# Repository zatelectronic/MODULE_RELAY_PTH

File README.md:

<div align="center">

# MODULE RELAY

**Módulo de relé com acionamento por nível alto (High Level Trigger), componentes totalmente através-furo (PTH), optoacoplador PC817 e relé de potência 12VDC / 15A**

</div>

---

## 📋 Índice

- [MODULE RELAY](#module-relay)
  - [📋 Índice](#-índice)
  - [Visão Geral](#visão-geral)
  - [Imagens do Projeto](#imagens-do-projeto)
  - [Diferenças em relação ao MODULE RELAY SMD](#diferenças-em-relação-ao-module-relay-smd)
  - [Funcionalidades](#funcionalidades)
  - [Diagrama de Funcionamento](#diagrama-de-funcionamento)
  - [Especificações Técnicas](#especificações-técnicas)
  - [Lista de Materiais](#lista-de-materiais)
  - [Pinagem dos Conectores](#pinagem-dos-conectores)
    - [J1 — Entrada (Controle)](#j1--entrada-controle)
    - [J2 — Saída (Carga)](#j2--saída-carga)
  - [Aplicações](#aplicações)
  - [Estrutura do Repositório](#estrutura-do-repositório)
  - [Como Usar](#como-usar)
    - [Conexão básica com Arduino / ESP32](#conexão-básica-com-arduino--esp32)
    - [Exemplo de código Arduino](#exemplo-de-código-arduino)
    - [Dica de Montagem](#dica-de-montagem)
  - [⚠️ Avisos de Segurança](#️-avisos-de-segurança)
  - [Sobre](#sobre)

---

## Visão Geral

**MODULE RELAY** é um módulo de acionamento de relé com **acionamento por optoacoplador** (a entrada +IN e a bobina usam o mesmo GND do borne J1: não há isolação galvânica entre controle e alimentação; os contatos do relé são isolados da bobina), projetado pela **ZAT ELECTRONIC** utilizando **KiCad 10**. Diferente da versão SMD, esta placa utiliza exclusivamente **componentes através-furo (PTH)**, tornando-a ideal para montagem manual, prototipagem e laboratórios maker.

O circuito utiliza o optoacoplador **PC817** (DIP-4 PTH) para acoplar o sinal de controle (proveniente de microcontroladores como Arduino, ESP32, etc.) do circuito de potência. O transistor **BC548** (TO-92 PTH) aciona a bobina do relé de potência 12VDC, capaz de comutar cargas de até **15A em 125VAC ou 24VDC**.

> ⚡ **High Level Trigger** — o relé é acionado com sinal lógico alto (+3,3V ou +5V) no pino de entrada, com o LED do optoacoplador como carga do pino do microcontrolador.

---

## Imagens do Projeto

<div align="center">

*Vista superior — relé de potência, optoacoplador PC817 DIP, transistor BC548 e bornes KRE*

<br/>

*Vista isométrica — componentes PTH, LED azul 5mm e layout geral da placa*

<br/>

<br/>

<br/>

</div>

---

## Diferenças em relação ao MODULE RELAY SMD

| Característica | MODULE RELAY (PTH) | MODULE RELAY SMD |
|----------------|-------------------|-----------------|
| **Tipo de montagem** | Através-furo (PTH) | Montagem superficial (SMD) |
| **Optoacoplador** | PC817 DIP-4 PTH | LTV-357T SOP-4 SMD |
| **Transistor driver** | BC548 (TO-92 PTH) | MMBT2222A (SOT-23 SMD) |
| **Resistores** | Axial 0,5W PTH | SMD 0805 |
| **LED de status** | 5mm PTH azul | SMD 0805 |
| **Diodo de roda livre** | 1N4007 PTH axial | S1M SMA SMD |
| **Facilidade de montagem** | Alta — soldagem manual simples | Requer soldagem SMD |
| **Público alvo** | Iniciantes, makers, laboratório | Produção, compacto, profissional |

---

## Funcionalidades

- ✅ **Relé de potência 12VDC / 15A** — contatos SPDT (NO, COMUM, NC), 15A 125VAC / 15A 24VDC
- ✅ **Optoacoplador PC817** (DIP-4 PTH) — aciona o driver; controle e bobina compartilham o GND
- ✅ **Transistor BC548** (TO-92 PTH) — driver NPN para acionamento da bobina
- ✅ **Diodo de roda livre 1N4007** (PTH axial) — proteção contra tensão reversa da bobina
- ✅ **LED azul 5mm PTH** — indicação visual de relé acionado
- ✅ **High Level Trigger** — compatível com 3,3V e 5V (Arduino, ESP32, Raspberry Pi, etc.)
- ✅ **Bornes KRE parafuso** (3 pinos, passo 5,0mm) — conexão robusta para entrada e saída
- ✅ **Todos os componentes PTH** — montagem manual fácil, ideal para prototipagem
- ✅ **Made in Brazil** — serigrafia na PCB

---

## Diagrama de Funcionamento

```
Microcontrolador / Sinal de Controle
        │
    +IN ●──[R1 220Ω]──► U1 PC817 (LED, pino 1) ── pino 2 ── GND
                               │ (acoplamento óptico)
    +12V ─────────────► U1 coletor (pino 4)
                        U1 emissor (pino 3) ──[R2 4,7kΩ]──┬──► Base Q1 BC548
                                                        [R4 10kΩ]
                                                          │
                                                         GND
    +12V ──┬──────────────┬─────────[R3 470Ω]──[D1 LED azul]──┐
       [Bobina K1]   [D2 1N4007] (roda livre)                 │
           └──────────────┴───────────────────────────────────┴──► Coletor Q1 (emissor no GND)

              Contatos do Relé (J2 — OUT)
         ┌────────────────────────────────┐
         │   NO  │  COMUM  │  NC          │
         └────────────────────────────────┘
          Carga: até 15A / 125VAC ou 24VDC
```

---

## Especificações Técnicas

| Parâmetro | Valor |
|-----------|-------|
| **Relé** | 12VDC / SPDT (Form C) |
| **Tensão da Bobina** | 12VDC |
| **Corrente máx. de carga (AC)** | 15A @ 125VAC |
| **Corrente máx. de carga (DC)** | 15A @ 24VDC |
| **Tipo de contato** | SPDT — NO, NC, COMUM |
| **Tensão de alimentação do módulo** | +12V |
| **Tensão de controle (sinal IN)** | 3,3V a 5V (High Level Trigger) |
| **Optoacoplador** | PC817 DIP-4 — GND comum com a bobina |
| **Transistor driver** | BC548 (TO-92, NPN) |
| **Diodo de proteção** | 1N4007 (PTH axial) |
| **LED de status** | 5mm PTH azul |
| **Resistores** | Axial 0,5W PTH |
| **Conectores** | Borne KRE parafuso 3 pinos, passo 5,0mm |
| **Ferramenta de Projeto** | KiCad 10 |
| **Tipo de montagem** | PTH — Através-furo |

---

## Lista de Materiais

| Ref | Componente | Valor / Parte | Encapsulamento |
|-----|-----------|--------------|----------------|
| K1 | Relé de Potência | AY1RC2 12VDC / 15A SPDT | PTH (pinagem SANYOU SRD) |
| U1 | Optoacoplador | PC817 | DIP-4 PTH |
| Q1 | Transistor NPN | BC548 | TO-92 PTH |
| D2 | Diodo de Roda Livre | 1N4007 | PTH Axial |
| D1 | LED de Status | LED 5mm Azul | PTH 5mm |
| R1 | Resistor de entrada (LED do opto) | 220Ω | Axial PTH |
| R2 | Resistor série da base | 4,7kΩ | Axial PTH |
| R4 | Resistor pull-down da base | 10kΩ | Axial PTH |
| R3 | Resistor do LED de status | 470Ω | Axial PTH |
| J1 | Borne de Entrada (Controle) | +12V, +IN, GND | KRE 3 pinos 5,0mm |
| J2 | Borne de Saída (Carga) | NO, COMUM, NC | KRE 3 pinos 5,0mm |

---

## Pinagem dos Conectores

### J1 — Entrada (Controle)

| Pino | Sinal | Descrição |
|------|-------|-----------|
| 1 | +12V | Alimentação da bobina do relé |
| 2 | +IN | Sinal de controle (3,3V–5V = relé ON) |
| 3 | GND | Terra comum |

### J2 — Saída (Carga)

| Pino | Sinal | Descrição |
|------|-------|-----------|
| 1 | NO | Normalmente aberto (fecha quando acionado) |
| 2 | COMUM | Terminal comum do relé |
| 3 | NC | Normalmente fechado (abre quando acionado) |

---

## Aplicações

- 🏠 **Automação residencial** — acionamento de lâmpadas, tomadas e ventiladores
- 🤖 **Projetos com Arduino e ESP32** — controle de cargas AC
- 🏫 **Ensino e prototipagem** — componentes PTH facilmente soldáveis e substituíveis
- 💡 **Controle de iluminação** — painéis de LED de alta potência e luminárias
- 🔌 **Comutação de cargas** — relé separa os contatos de carga da bobina (GND de controle e de alimentação é comum)
- 📡 **IoT e domótica** — integração com sistemas MQTT, Home Assistant, etc.

---

## Estrutura do Repositório

```
MODULE_RELAY_PTH/
├── MODULE_RELAY_PTH.kicad_pro    # Arquivo de projeto KiCad 10
├── MODULE_RELAY_PTH.kicad_sch    # Esquemático: capa A2 (índice das folhas)
├── RELAY.kicad_sch               # Folha 02: optoacoplador + driver + relé
├── CONN.kicad_sch                # Folha 03: bornes IN / OUT + PWR_FLAG
├── MODULE_RELAY_PTH.kicad_pcb    # Layout da PCB (KiCad 10)
├── MODULE_RELAY_PTH.kicad_prl    # Configurações locais
├── MODULE_RELAY_PTH.kicad_dru    # Regra: GND a 3 mm dos contatos do relé
├── Zat_TitleBlock.kicad_wks      # Title block ZAT ELECTRONIC
├── packages3D/                   # Modelos 3D arquivados (referência)
├── imagem_1.png                  # Render 3D superior
├── imagem_2.png                  # Render 3D isométrico
├── LEIA-ME_REVISAO_R01.md        # O que mudou na revisão R01
└── README.md
```

---

## Como Usar

### Conexão básica com Arduino / ESP32

```
Arduino / ESP32             MODULE RELAY
───────────────────         ─────────────────
GND              ────────►  J1 - GND
Pino digital     ────────►  J1 - +IN

Fonte 12VDC (+)  ────────►  J1 - +12V
Fonte 12VDC (-)  ────────►  J1 - GND

Carga AC/DC      ────────►  J2 - COMUM + NO (ou NC)
```

### Exemplo de código Arduino

```cpp
#define RELAY_PIN 7

void setup() {
  pinMode(RELAY_PIN, OUTPUT);
  digitalWrite(RELAY_PIN, LOW); // relé desligado na inicialização
}

void loop() {
  digitalWrite(RELAY_PIN, HIGH); // aciona o relé
  delay(1000);
  digitalWrite(RELAY_PIN, LOW);  // desaciona o relé
  delay(1000);
}
```

### Dica de Montagem

> 🔧 Por ser totalmente PTH, recomenda-se a seguinte ordem de soldagem: resistores primeiro, depois diodo, transistor BC548, optoacoplador PC817, LED, relé e por último os bornes KRE.

## ⚠️ Avisos de Segurança

> 🔴 **ATENÇÃO — TENSÕES PERIGOSAS**

- Este módulo pode comutar tensões de **rede elétrica (110V / 220V AC)**. Manuseie com extremo cuidado.
- **Nunca toque nos terminais J2 (OUT)** enquanto houver carga CA conectada e o circuito energizado.
- Utilize **caixa de proteção** adequada quando instalar em ambientes com acesso de pessoas.
- Respeite a **corrente máxima de 15A** nos contatos do relé.
- O optoacoplador **não isola** o GND do microcontrolador do GND do módulo (são comuns no J1) e **não substitui normas de segurança elétrica**.
- A zona GND fica a 3 mm das trilhas e pads dos contatos do relé (COMUM / NO / NC), por regra no MODULE_RELAY_PTH.kicad_dru. Conferir a creepage exigida pela norma da aplicação final.
- Projeto destinado a **profissionais e experimentadores experientes**.

---

## Sobre

<div align="center">

Projetado por **ZAT ELECTRONIC**

*MODULE RELAY — Made in Brazil 🇧🇷*

</div>>

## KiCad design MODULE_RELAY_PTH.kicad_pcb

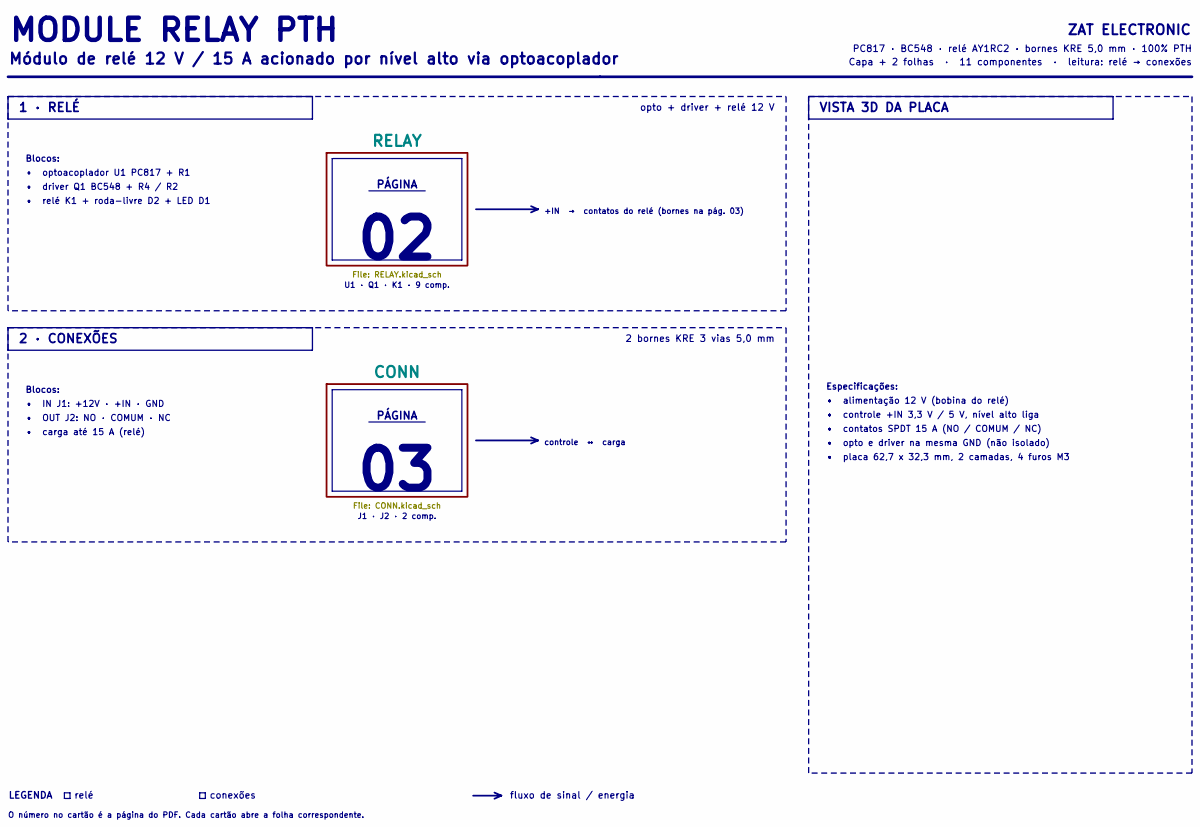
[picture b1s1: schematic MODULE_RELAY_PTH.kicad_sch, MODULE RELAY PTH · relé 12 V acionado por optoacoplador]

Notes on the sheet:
O número no cartão é a página do PDF. Cada cartão abre a folha correspondente.
fluxo de sinal / energia
conexões
controle ↔ carga
• driver Q1 BC548 + R4 / R2
2 bornes KRE 3 vias 5,0 mm
+IN → contatos do relé (bornes na pág. 03)
Blocos:
1 · RELÉ
ZAT ELECTRONIC
Módulo de relé 12 V / 15 A acionado por nível alto via optoacoplador
LEGENDA
J1 · J2 · 2 comp.
• controle +IN 3,3 V / 5 V, nível alto liga
opto + driver + relé 12 V
• opto e driver na mesma GND (não isolado)
• contatos SPDT 15 A (NO / COMUM / NC)
• carga até 15 A (relé)
• OUT J2: NO · COMUM · NC
• relé K1 + roda-livre D2 + LED D1
• optoacoplador U1 PC817 + R1
PC817 · BC548 · relé AY1RC2 · bornes KRE 5,0 mm · 100% PTH
relé
PÁGINA
2 · CONEXÕES
Capa + 2 folhas · 11 componentes · leitura: relé → conexões
• placa 62,7 x 32,3 mm, 2 camadas, 4 furos M3
• alimentação 12 V (bobina do relé)
U1 · Q1 · K1 · 9 comp.
• IN J1: +12V · +IN · GND
MODULE RELAY PTH
Especificações:
VISTA 3D DA PLACA

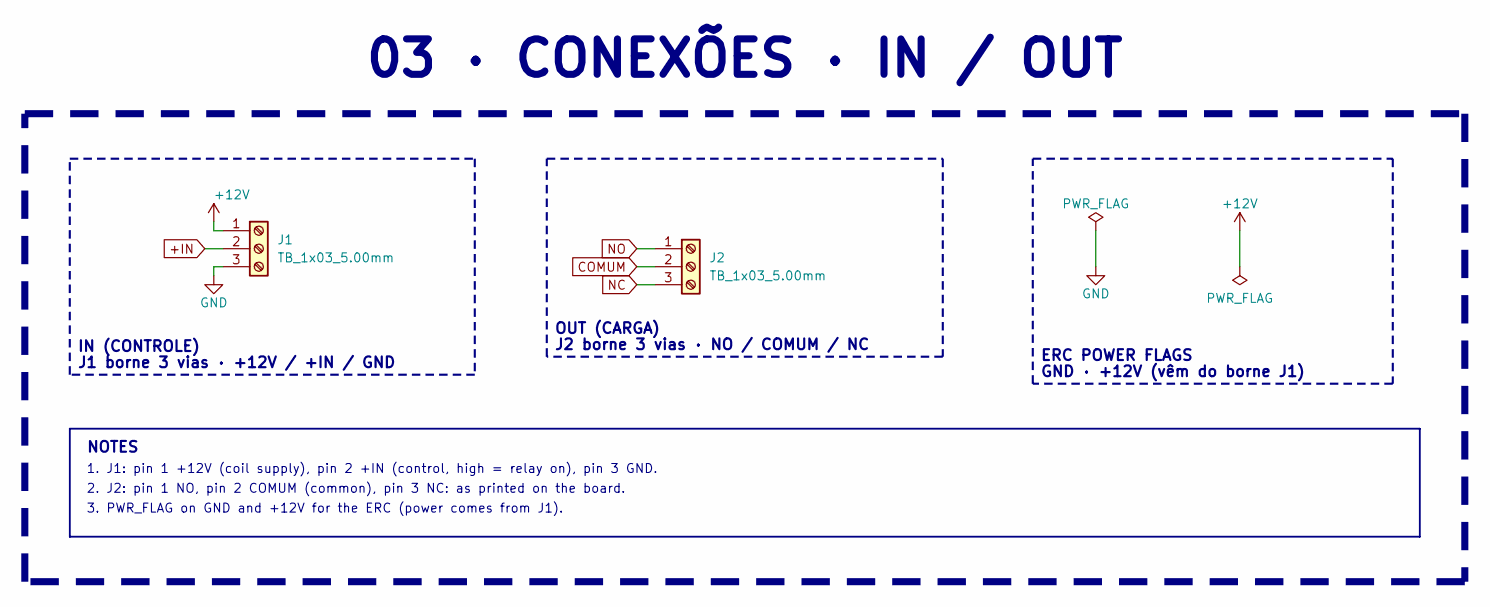
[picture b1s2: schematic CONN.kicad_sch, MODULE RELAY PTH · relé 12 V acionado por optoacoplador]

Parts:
J1, J2: TB_1x03_5.00mm; TerminalBlock_MaiXu_MX126-5.0-03P_1x03_P5.00mm_DG306

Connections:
+12V: J1.1; also elsewhere on the board
+IN: J1.2; also elsewhere on the board
COMUM: J2.2; also elsewhere on the board
GND: J1.3; also elsewhere on the board
NC: J2.3; also elsewhere on the board
NO: J2.1; also elsewhere on the board

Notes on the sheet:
NOTES
1. J1: pin 1 +12V (coil supply), pin 2 +IN (control, high = relay on), pin 3 GND.
3. PWR_FLAG on GND and +12V for the ERC (power comes from J1).
03 · CONEXÕES · IN / OUT
J2 borne 3 vias · NO / COMUM / NC
IN (CONTROLE)
GND · +12V (vêm do borne J1)
OUT (CARGA)
ERC POWER FLAGS
2. J2: pin 1 NO, pin 2 COMUM (common), pin 3 NC: as printed on the board.
J1 borne 3 vias · +12V / +IN / GND

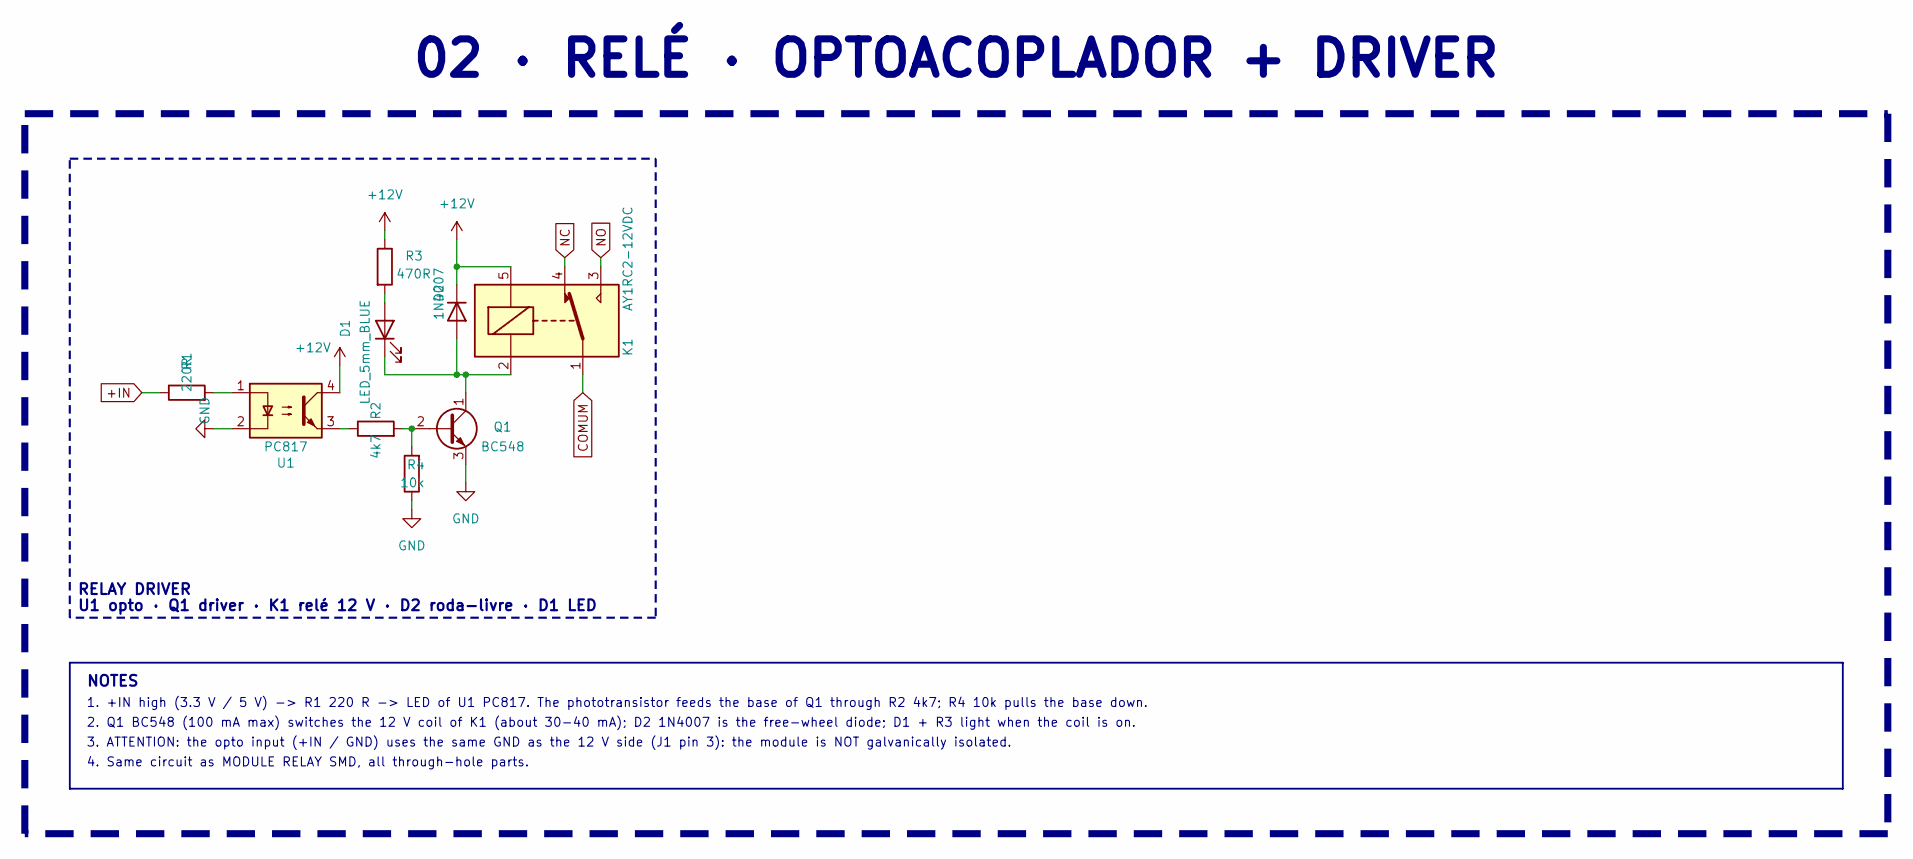
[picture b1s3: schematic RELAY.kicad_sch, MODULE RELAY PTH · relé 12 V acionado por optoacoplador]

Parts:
D1: LED_5mm_BLUE; LED_D5.0mm_Blue
D2: 1N4007; D_DO-41_SOD81_P10.16mm_Horizontal_1N4007
K1: AY1RC2-12VDC; Relay_SPDT_SANYOU_SRD_Series_Form_C_AY1RC2
Q1: BC548; TO-92_HandSolder_BC548
R1: 220R; R_Axial_DIN0204_L3.6mm_D1.6mm_P7.62mm_Horizontal_220R
R2: 4k7; R_Axial_DIN0204_L3.6mm_D1.6mm_P7.62mm_Horizontal_4K7
R3: 470R; R_Axial_DIN0204_L3.6mm_D1.6mm_P7.62mm_Horizontal_470R
R4: 10k; R_Axial_DIN0204_L3.6mm_D1.6mm_P7.62mm_Horizontal_10K
U1: PC817; DIP-4_W7.62mm_LongPads_PC817

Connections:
+12V: D2.1 (K), K1.5, R3.1, U1.4; also elsewhere on the board
+IN: R1.1; also elsewhere on the board
COMUM: K1.1; also elsewhere on the board
GND: Q1.3 (E), R4.1, U1.2; also elsewhere on the board
NC: K1.4; also elsewhere on the board
NO: K1.3; also elsewhere on the board
unnamed: D1.2 (A), R3.2
unnamed: D1.1 (K), D2.2 (A), K1.2, Q1.1 (C)
unnamed: Q1.2 (B), R2.2, R4.2
unnamed: R1.2, U1.1
unnamed: R2.1, U1.3

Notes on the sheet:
4. Same circuit as MODULE RELAY SMD, all through-hole parts.
1. +IN high (3.3 V / 5 V) -> R1 220 R -> LED of U1 PC817. The phototransistor feeds the base of Q1 through R2 4k7; R4 10k pulls the base down.
02 · RELÉ · OPTOACOPLADOR + DRIVER
RELAY DRIVER
U1 opto · Q1 driver · K1 relé 12 V · D2 roda-livre · D1 LED
NOTES
3. ATTENTION: the opto input (+IN / GND) uses the same GND as the 12 V side (J1 pin 3): the module is NOT galvanically isolated.
2. Q1 BC548 (100 mA max) switches the 12 V coil of K1 (about 30-40 mA); D2 1N4007 is the free-wheel diode; D1 + R3 light when the coil is on.

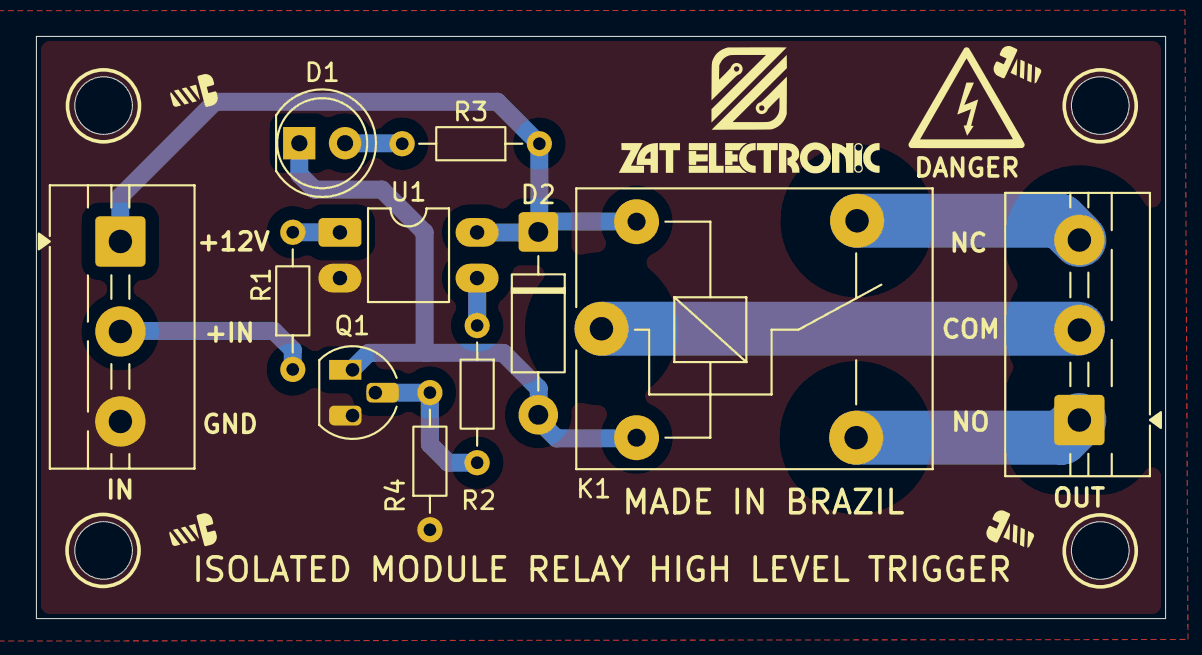
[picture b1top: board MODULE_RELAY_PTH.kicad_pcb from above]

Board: 2 copper layers, 62.7 x 32.3 mm, 15 parts (0 on the bottom side), 11 nets.

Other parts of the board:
H1, H2, H3, H4: MountingHole_3.2mm_M3

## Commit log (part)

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2026-06-28 commit_3
2026-06-29 COMMIT-4
2026-06-29 COMMIT-5
